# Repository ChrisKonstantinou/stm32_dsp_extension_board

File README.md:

# guitar-pedal
 A multi effect guitar pedal

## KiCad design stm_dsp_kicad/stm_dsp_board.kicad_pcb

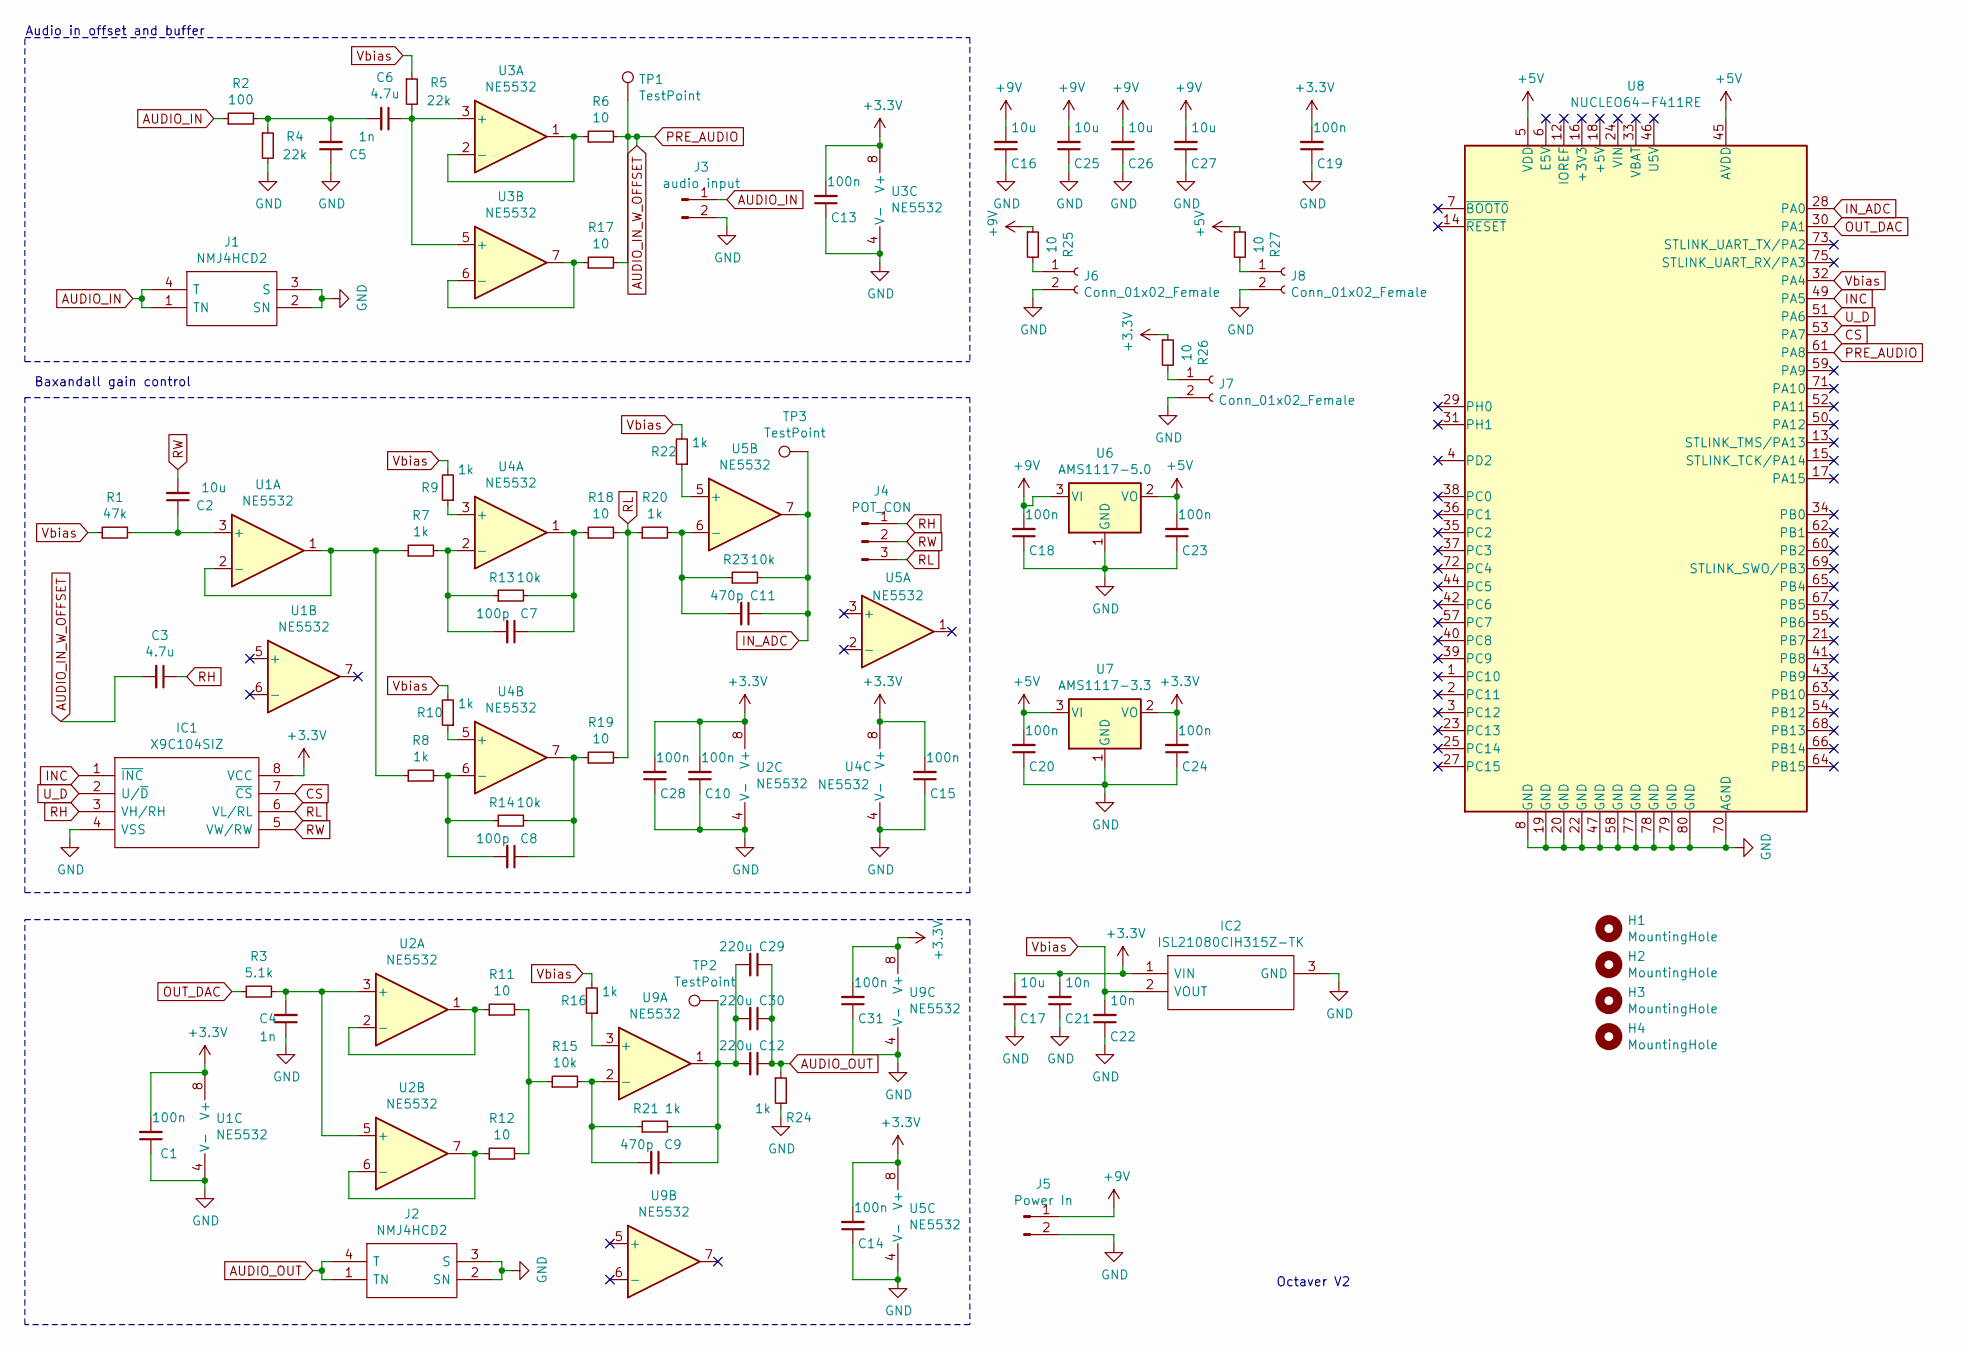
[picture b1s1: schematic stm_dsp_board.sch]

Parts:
C1, C10, C13, C14, C15, C18, C19, C20, C23, C24, C28, C31: 100n; C_1206_3216Metric_Pad1.42x1.75mm_HandSolder
C2, C16, C17: 10u; C_1206_3216Metric_Pad1.42x1.75mm_HandSolder
C3, C6: 4.7u; C_1206_3216Metric_Pad1.42x1.75mm_HandSolder
C4, C5: 1n; C_1206_3216Metric_Pad1.42x1.75mm_HandSolder
C7, C8: 100p; C_1206_3216Metric_Pad1.42x1.75mm_HandSolder
C9, C11: 470p; C_1206_3216Metric_Pad1.42x1.75mm_HandSolder
C12, C29, C30: 220u; CP_Radial_D8.0mm_P5.00mm
C21, C22: 10n; C_1206_3216Metric_Pad1.42x1.75mm_HandSolder
C25, C26, C27: 10u; CP_Radial_D8.0mm_P5.00mm
H1, H2, H3, H4: MountingHole; MountingHole_4.5mm_Pad
IC1: X9C104SIZ; SOIC127P600X175-8N; Mouser Part Number 968-X9C104SIZ
IC2: ISL21080CIH315Z-TK; SOT95P237X112-3N; Mouser Part Number 968-ISL21080CIH315ZT
J1, J2: NMJ4HCD2; Mouser Part Number 550-12202
J3: audio input; PinHeader_1x02_P2.54mm_Vertical
J4: POT_CON; PinHeader_1x03_P2.54mm_Vertical
J5: Power In; TerminalBlock_bornier-2_P5.08mm
J6, J7, J8: Conn_01x02_Female; PinHeader_1x02_P2.54mm_Vertical
R1: 47k; R_1206_3216Metric_Pad1.42x1.75mm_HandSolder
R2: 100; R_1206_3216Metric_Pad1.42x1.75mm_HandSolder
R3: 5.1k; R_1206_3216Metric_Pad1.42x1.75mm_HandSolder
R4, R5: 22k; R_1206_3216Metric_Pad1.42x1.75mm_HandSolder
R6, R11, R12, R17, R18, R19, R25, R26, R27: 10; R_1206_3216Metric_Pad1.42x1.75mm_HandSolder
R7, R8, R9, R10, R16, R20, R21, R22, R24: 1k; R_1206_3216Metric_Pad1.42x1.75mm_HandSolder
R13, R14, R15, R23: 10k; R_1206_3216Metric_Pad1.42x1.75mm_HandSolder
TP1, TP2, TP3: TestPoint; PinHeader_1x01_P2.54mm_Vertical
U1, U2, U3, U4, U5, U9: NE5532; NE555DR
U6: AMS1117-5.0; SOT-223-3_TabPin2
U7: AMS1117-3.3; SOT-223-3_TabPin2
U8: NUCLEO64-F411RE; nucleo64

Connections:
+3V3: C1.2, C10.2, C13.2, C14.2, C15.2, C17.2, C19.2, C21.2, C24.2, C28.2, C31.2, IC1.8 (VCC), IC2.1 (VIN), R26.1, U1.8 (V+), U2.8 (V+), U3.8 (V+), U4.8 (V+), U5.8 (V+), U7.2 (VO), U9.8 (V+)
+5V: C20.2, C23.2, R27.1, U6.2 (VO), U7.3 (VI), U8.5 (VDD), U8.45 (AVDD)
+9V: C16.2, C18.2, C25.2, C26.2, C27.2, J5.1, R25.1, U6.3 (VI)
AUDIO_IN: J1.1 (TN), J1.4 (T), J3.1, R2.1
AUDIO_IN_W_OFFSET: C3.2, R6.2, R17.2, TP1.1, U8.61 (PA8)
AUDIO_OUT: C12.1, C29.1, C30.1, J2.1 (TN), J2.4 (T), R24.1
CS: IC1.7 (~CS), U8.53 (PA7)
GND: C1.1, C4.1, C5.1, C10.1, C13.1, C14.1, C15.1, C16.1, C17.1, C18.1, C19.1, C20.1, C21.1, C22.1, C23.1, C24.1, C25.1, C26.1, C27.1, C28.1, C31.1, IC1.4 (VSS), IC2.3 (GND), J1.2 (SN), J1.3 (S), J2.2 (SN), J2.3 (S), J3.2, J5.2, J6.2, J7.2, J8.2, R4.2, R24.2, U1.4 (V-), U2.4 (V-), U3.4 (V-), U4.4 (V-), U5.4 (V-), U6.1 (GND), U7.1 (GND), U8.8 (GND), U8.19 (GND), U8.20 (GND), U8.22 (GND), U8.47 (GND), U8.58 (GND), U8.70 (AGND), U8.77 (GND), U8.78 (GND), U8.79 (GND), U8.80 (GND), U9.4 (V-)
INC: IC1.1 (~INC), U8.49 (PA5)
IN_ADC: C11.1, R23.2, TP3.1, U5.7, U8.28 (PA0)
unnamed: C2.1, R1.2, U1.3 (+)
unnamed: C4.2, R3.2, U2.3 (+), U2.5 (+)
unnamed: C5.2, C6.2, R2.2, R4.1
unnamed: C6.1, R5.2, U3.3 (+), U3.5 (+)
unnamed: C7.1, R13.2, R18.1, U4.1
unnamed: C7.2, R7.2, R13.1, U4.2 (-)
unnamed: C8.1, R14.2, R19.1, U4.7
unnamed: C8.2, R8.2, R14.1, U4.6 (-)
unnamed: C9.2, R15.2, R21.1, U9.2 (-)
unnamed: C11.2, R20.2, R23.1, U5.6 (-)
unnamed: C9.1, C12.2, C29.2, C30.2, R21.2, TP2.1, U9.1
unnamed: J6.1, R25.2
unnamed: J7.1, R26.2
unnamed: J8.1, R27.2
unnamed: R6.1, U3.1, U3.2 (-)
unnamed: R7.1, R8.1, U1.1, U1.2 (-)
unnamed: R9.1, U4.3 (+)
unnamed: R10.1, U4.5 (+)
unnamed: R11.1, U2.1, U2.2 (-)
unnamed: R11.2, R12.2, R15.1
unnamed: R12.1, U2.6 (-), U2.7
unnamed: R16.1, U9.3 (+)
unnamed: R17.1, U3.6 (-), U3.7
unnamed: R22.1, U5.5 (+)
OUT_DAC: R3.1, U8.30 (PA1)
RH: C3.1, IC1.3 (VH/RH), J4.1
RL: IC1.6 (VL/RL), J4.3, R18.2, R19.2, R20.1
RW: C2.2, IC1.5 (VW/RW), J4.2
U_D: IC1.2 (U/~D), U8.51 (PA6)
Vbias: C22.2, IC2.2 (VOUT), R1.1, R5.1, R9.2, R10.2, R16.2, R22.2, U8.32 (PA4)

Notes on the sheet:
Octaver V2
Baxandall gain control
Audio in offset and buffer

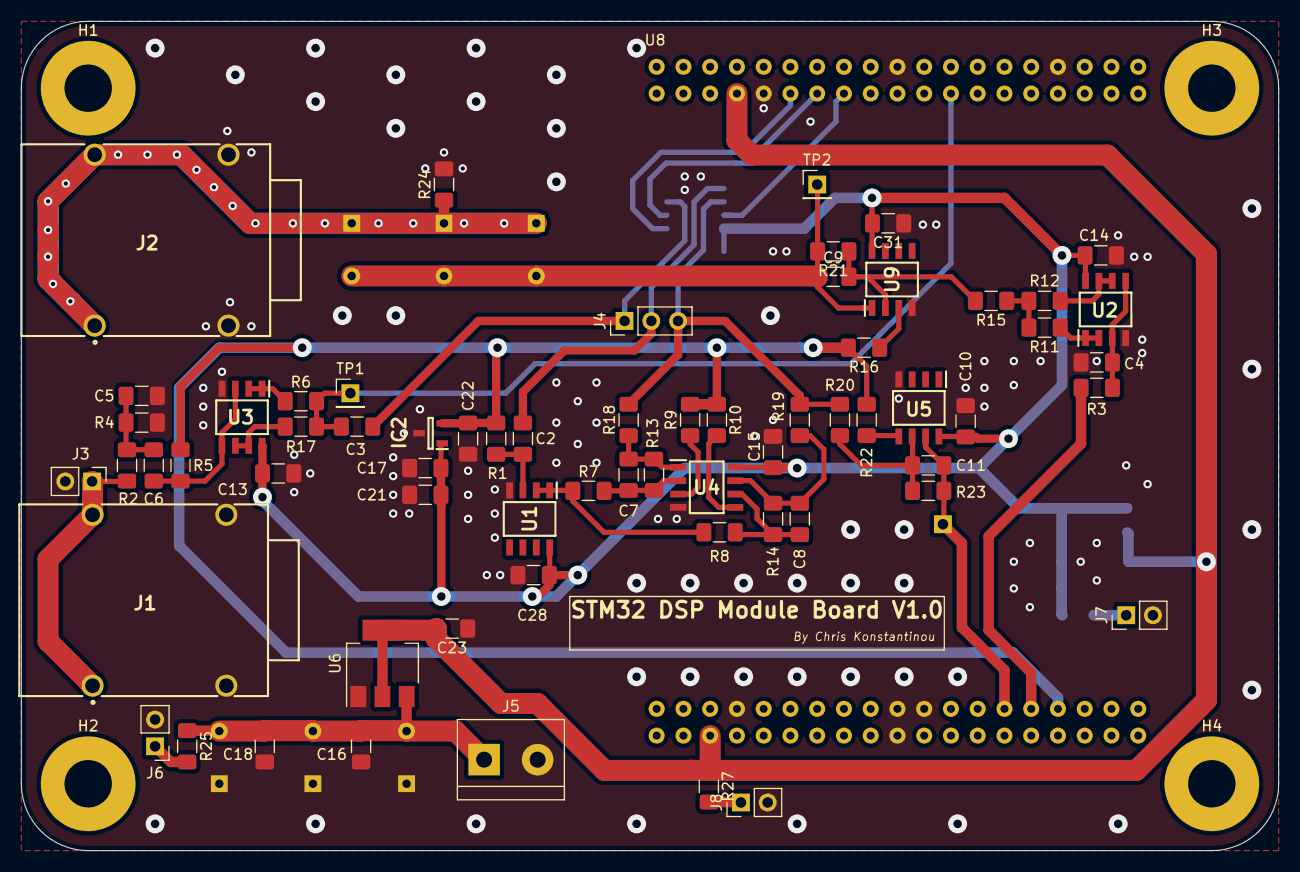
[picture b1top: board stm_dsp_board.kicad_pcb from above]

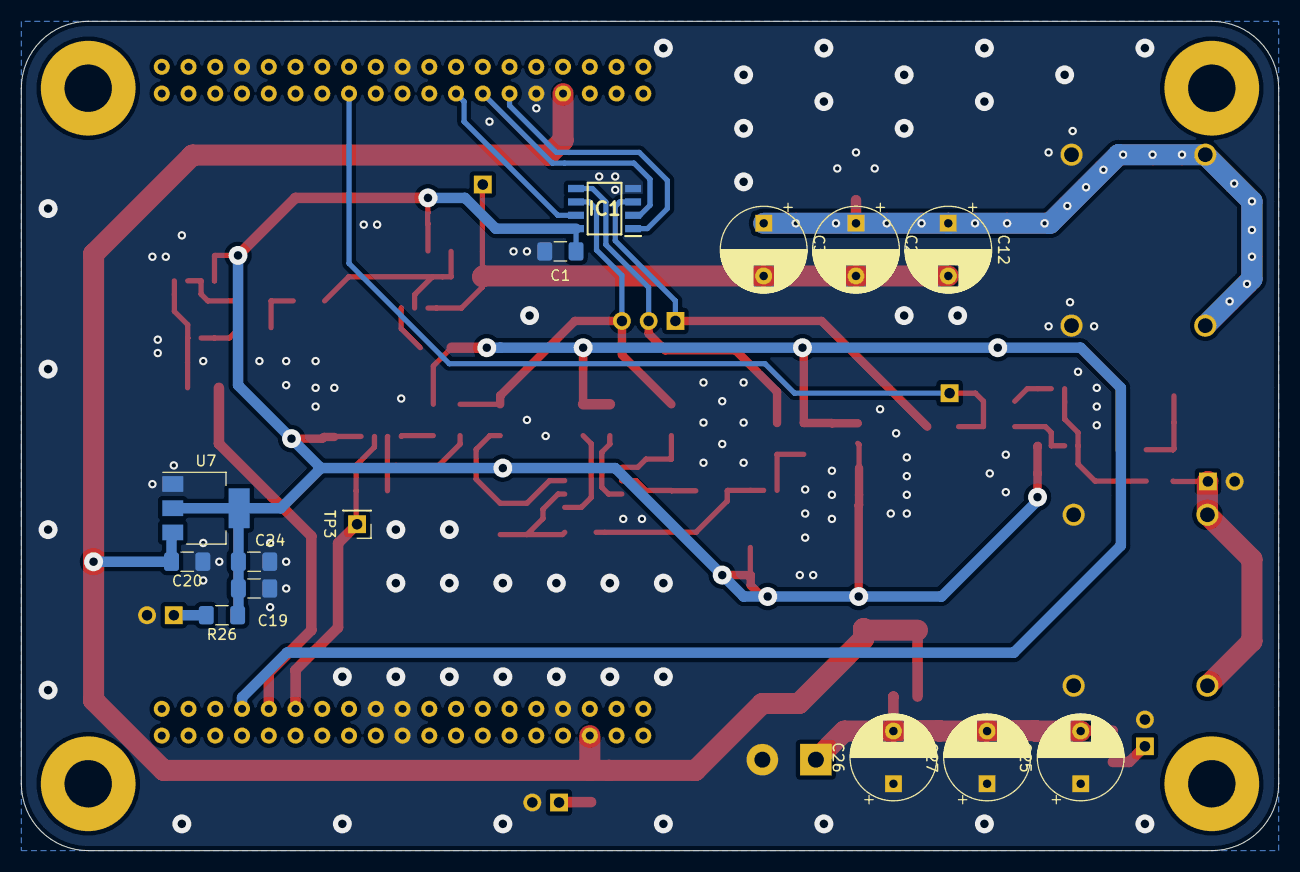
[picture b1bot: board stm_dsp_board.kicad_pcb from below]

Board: 2 copper layers, 119.4 x 78.7 mm, 84 parts (14 on the bottom side), 40 nets.

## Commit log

2021-12-23 Added all local files
2021-12-24 Added resque files
2022-07-09 Update project structure
